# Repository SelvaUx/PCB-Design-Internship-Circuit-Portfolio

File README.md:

<h1 align="center">⚡ PCB Design Internship — Circuit Portfolio</h1>

<p align="center">
  <strong>A collection of 10 production-ready schematic & PCB layout designs</strong><br/>
  <em>From fundamental analog circuits to motor control systems — all designed in KiCad</em>
</p>

---

## 👤 About the Author

**Selva Pandi** — _Selva.Ux_ online

> An ECE student who decided that waiting to be qualified was a worse plan than just building the thing.

I build for the messy, low-bandwidth, real world — where people need technology that actually functions. My engineering philosophy is simple: **offline first, privacy always, real hardware required**. I don't trust solutions that work only in ideal conditions.

From custom AI assistants to fiber fault detection engines, from IoT aquaculture platforms to portfolio sites with mini-labs inside — the list doesn't stop because the curiosity doesn't stop.

|                        |                                                            |
| ---------------------- | ---------------------------------------------------------- |
| 🌐 **Portfolio + Lab** | [selvaux.in](https://selvaux.in)                           |
| 📫 **Email**           | [selva.ux@yahoo.com](mailto:selva.ux@yahoo.com)            |
| 💡 **Specialization**  | Offline AI · Edge Computing · Embedded Systems · Custom OS |

---

## 🛠️ Tools & Technologies

| Tool                                            | Purpose                                                             |
| ----------------------------------------------- | ------------------------------------------------------------------- |
| [**KiCad EDA**](https://www.kicad.org/) (v10.0) | Primary CAD suite                                                   |
| **Eeschema**                                    | Schematic capture, including hierarchical multi-sheet designs       |
| **Pcbnew**                                      | PCB routing, footprint assignment, copper zone fills & board layout |
| **SPICE**                                       | Integrated simulation models for circuit verification               |

---

## 📂 Repository Structure

```
📦 Iternship PCB/
├── 🌉 Bridge Rectifier/          → Full-wave AC-to-DC rectifier
├── 🚨 Buzzer Alarm/              → Transistor-driven buzzer with push-button
├── 💡 LED Blink Using IC555/     → Astable multivibrator LED flasher
├── 🔌 LED Circuit/               → Multi-LED driver with transistor switching
├── 📉 Low Pass Filter/           → Passive RC low-pass filter
├── 🎵 METRONOME/                 → 555 Timer metronome with speaker output
├── ⚙️ Motor Speed Controller/    → PWM DC motor speed control via L293 H-Bridge
├── 💡 Simple LED Circuit/        → Hierarchical push-button LED (multi-sheet)
├── ⚡ Voltage Divider/           → Two-resistor voltage divider
├── 🔌 Voltage Regulator/         → +5V linear regulated power supply
└── 📄 README.md
```

Each project folder contains:

```text
├── [Project].kicad_pro     # KiCad Project File
├── [Project].kicad_sch     # Main Schematic (or Parent Sheet)
├── [Project].kicad_pcb     # PCB Layout File
├── [Project].kicad_prl     # Project Local Settings
├── [Sub-sheets].kicad_sch  # Sub-schematics (hierarchical designs only)
└── .history/               # KiCad automatic local history backups
```

---

## 📋 Projects Catalog

### 1. 🌉 Bridge Rectifier

|               |                                               |
| ------------- | --------------------------------------------- |
| **Category**  | Power Electronics — AC/DC Conversion          |
| **Schematic** | `Bridge Rectifier/Bridge Rectifier.kicad_sch` |
| **PCB**       | `Bridge Rectifier/Bridge Rectifier.kicad_pcb` |

**Circuit Goal:** Converts a dual AC voltage source into a smoothed, single-polarity DC output.

**Bill of Materials:**

| Ref    | Component                        | Value    | Purpose                    |
| ------ | -------------------------------- | -------- | -------------------------- |
| D1–D4  | `1N4007` Rectifier Diode         | —        | Bridge configuration       |
| C1     | Polarized Electrolytic Capacitor | `4000µF` | Ripple smoothing reservoir |
| R1     | Resistor                         | `1kΩ`    | Load / bleeder resistor    |
| V1, V2 | Sinusoidal AC Source             | `12V`    | Simulation sources         |

**How It Works:** The four diodes form a bridge that rectifies both halves of the AC waveform. The large `4000µF` capacitor acts as a low-pass reservoir to minimize voltage ripple, delivering a stable DC output across `R1`.

---

### 2. 🚨 Buzzer Alarm

|               |                                       |
| ------------- | ------------------------------------- |
| **Category**  | Digital Logic — Transistor Switching  |
| **Schematic** | `Buzzer Alarm/Buzzer Alarm.kicad_sch` |
| **PCB**       | `Buzzer Alarm/Buzzer Alarm.kicad_pcb` |

**Circuit Goal:** A transistor-driven active buzzer alarm actuated by a manual push-button switch.

**Bill of Materials:**

| Ref | Component          | Value  | Purpose                    |
| --- | ------------------ | ------ | -------------------------- |
| BZ1 | Active Buzzer      | —      | Sound output               |
| Q1  | `BC547` NPN BJT    | —      | Low-side electronic switch |
| SW1 | Push Button (SPST) | —      | Manual trigger             |
| R1  | Resistor           | `10kΩ` | Base current-limiting      |
| R2  | Resistor           | `1kΩ`  | Bias resistor              |

**How It Works:** The `BC547` transistor acts as a low-side switch. Pressing `SW1` drives base current into `Q1` via `R1`, saturating the transistor and allowing current to flow through the buzzer to ground.

---

### 3. ⏱️ LED Blink Using IC555

|               |                                                         |
| ------------- | ------------------------------------------------------- |
| **Category**  | Timing & Oscillation — Astable Multivibrator            |
| **Schematic** | `LED Blink Using IC555/LED Blink Using IC555.kicad_sch` |
| **PCB**       | `LED Blink Using IC555/LED Blink Using IC555.kicad_pcb` |

**Circuit Goal:** A classic 555 Timer astable oscillator that pulses an LED indicator at a defined frequency.

**Bill of Materials:**

| Ref | Component            | Value    | Purpose                           |
| --- | -------------------- | -------- | --------------------------------- |
| U1  | `NA555P` Timer IC    | —        | Oscillator core                   |
| R1  | Timing Resistor      | `1MΩ`    | Controls charge time T_high       |
| R2  | Timing Resistor      | `1MΩ`    | Controls charge & discharge T_low |
| C1  | Timing Capacitor     | `1.5nF`  | RC timing element                 |
| C2  | Bypass Capacitor     | `0.01µF` | Control voltage pin decoupling    |
| D1  | Red LED              | —        | Pulse indicator                   |
| R3  | Resistor             | `470Ω`   | LED current-limiting              |
| J1  | 2-pin Screw Terminal | —        | Power input connector             |

**How It Works:** The 555 continuously charges and discharges `C1` between ⅓ and ⅔ of VCC through `R1` and `R2`. This produces a continuous square wave on pin 3 (Output), causing LED `D1` to flash at a rate defined by:

$$f = \frac{1.44}{(R1 + 2 \cdot R2) \cdot C1}$$

---

### 4. 🔌 LED Circuit

|               |                                         |
| ------------- | --------------------------------------- |
| **Category**  | Transistor Switching — Multi-LED Driver |
| **Schematic** | `LED Circuit/LED Circuit.kicad_sch`     |
| **PCB**       | `LED Circuit/LED Circuit.kicad_pcb`     |

**Circuit Goal:** A multi-channel LED driver circuit using `BC547` NPN transistors as electronic switches, each controlling individual LEDs through current-limiting resistors.

**Bill of Materials:**

| Ref   | Component       | Value  | Purpose               |
| ----- | --------------- | ------ | --------------------- |
| BT1   | Battery Cell    | —      | DC power source       |
| Q1–Q3 | `BC547` NPN BJT | —      | LED driver switches   |
| D1–D9 | LEDs            | —      | Light indicators      |
| R1–R3 | Resistor        | `470Ω` | LED current-limiting  |
| R4–R6 | Resistor        | `10kΩ` | Base current-limiting |
| C1–C3 | Capacitor       | —      | Decoupling / timing   |

**How It Works:** Each `BC547` transistor is independently driven via a base resistor. When the transistor is saturated, it provides a ground path for the corresponding LED string. The `470Ω` resistors limit LED forward current, and `10kΩ` resistors control transistor base drive. This design demonstrates parallel transistor switching for multi-LED arrays.

---

### 5. 📉 Low Pass Filter

|               |                                             |
| ------------- | ------------------------------------------- |
| **Category**  | Signal Conditioning — Passive Filter        |
| **Schematic** | `Low Pass Filter/Low Pass Filter.kicad_sch` |
| **PCB**       | `Low Pass Filter/Low Pass Filter.kicad_pcb` |

**Circuit Goal:** A basic passive single-pole RC Low Pass Filter (LPF).

**Bill of Materials:**

| Ref | Component            | Value | Purpose        |
| --- | -------------------- | ----- | -------------- |
| R1  | Resistor             | `1kΩ` | Filter element |
| C1  | Polarized Capacitor  | `1µF` | Filter element |
| J1  | 2-pin Screw Terminal | —     | I/O connector  |

**How It Works:** Attenuates high-frequency signals while passing lower-frequency components. The cutoff frequency is:

$$f_c = \frac{1}{2\pi \cdot R1 \cdot C1} \approx 159.15 \text{ Hz}$$

Signals above this frequency are progressively attenuated at –20 dB/decade.

---

### 6. 🎵 METRONOME

|               |                                          |
| ------------- | ---------------------------------------- |
| **Category**  | Timing & Audio — Audible Click Generator |
| **Schematic** | `METRONOME/METRONOME.kicad_sch`          |
| **PCB**       | `METRONOME/METRONOME.kicad_pcb`          |

**Circuit Goal:** A 555 Timer-based electronic metronome that generates periodic audible clicks through a speaker, with adjustable tempo via a variable resistor (potentiometer).

**Bill of Materials:**

| Ref   | Component         | Value | Purpose                       |
| ----- | ----------------- | ----- | ----------------------------- |
| IC555 | 555 Timer IC      | —     | Astable oscillator core       |
| BT1   | Battery Cell      | —     | DC power source               |
| LS1   | Speaker           | —     | Audio output (CUI CMR-1206S)  |
| R1    | Resistor          | —     | Timing resistor               |
| R2    | Variable Resistor | —     | Tempo control (potentiometer) |
| R3    | Variable Resistor | —     | Fine tuning                   |
| C1–C3 | Capacitors        | —     | Timing & decoupling           |

**How It Works:** The 555 Timer runs in astable mode, generating a square wave output. The variable resistors `R2` and `R3` allow the user to adjust the oscillation frequency (tempo). The output drives a speaker `LS1` to produce rhythmic audible clicks. The timing capacitor and RC network set the beat interval.

---

### 7. ⚙️ Motor Speed Controller

|               |                                                           |
| ------------- | --------------------------------------------------------- |
| **Category**  | Motor Control — PWM Speed Regulation                      |
| **Schematic** | `Motor Speed Controller/Motor Speed Controller.kicad_sch` |
| **PCB**       | `Motor Speed Controller/Motor Speed Controller.kicad_pcb` |

**Circuit Goal:** A PWM-based DC motor speed controller using a 555 Timer IC for pulse generation and an L293 Quadruple Half-H Driver for motor drive, with flyback protection and direction control.

**Bill of Materials:**

| Ref    | Component              | Value  | Purpose                           |
| ------ | ---------------------- | ------ | --------------------------------- |
| U1     | `ICM7555xP` Timer IC   | —      | PWM pulse generator (astable)     |
| U2     | `L293` Motor Driver    | —      | Quadruple Half-H bridge driver    |
| M1     | DC Motor               | —      | Load                              |
| D2, D3 | `1N4001` Diode         | —      | Flyback / freewheeling protection |
| SW1    | Nidec CAS-120A1 Switch | —      | Motor on/off control              |
| R1     | Resistor               | `1kΩ`  | Timing / bias                     |
| R2, R4 | Resistor               | `100Ω` | Current limiting                  |
| R3     | Resistor               | —      | Timing                            |
| C1     | Polarized Capacitor    | `10µF` | Timing / decoupling               |
| J1     | 2-pin Screw Terminal   | —      | Power input connector             |

**How It Works:** The `ICM7555` generates a variable-duty-cycle PWM signal that feeds into the L293 H-Bridge driver's enable and input pins. By varying the duty cycle, the average voltage delivered to the DC motor changes, controlling its speed. The `1N4001` diodes provide flyback protection against voltage spikes from the motor's inductive load. The L293 handles the power switching, isolating the low-power timer circuit from the high-current motor.

---

### 8. 💡 Simple LED Circuit

|               |                                                            |
| ------------- | ---------------------------------------------------------- |
| **Category**  | Digital Basics — Hierarchical Design                       |
| **Schematic** | `Simple LED Circuit/Simple LED Circuit.kicad_sch` (Master) |
| **PCB**       | `Simple LED Circuit/Simple LED Circuit.kicad_pcb`          |

**Circuit Goal:** A modular, push-button-activated LED circuit using a **multi-sheet hierarchical design** in KiCad.

**Schematic Architecture:**

| Sheet                                       | Components                                 | Role                        |
| ------------------------------------------- | ------------------------------------------ | --------------------------- |
| **Master** (`Simple LED Circuit.kicad_sch`) | —                                          | Declares & links sub-sheets |
| **Power** (`power.kicad_sch`)               | `BT2`: Battery, `SW2`: Push Button         | Power supply & control      |
| **LED** (`led.kicad_sch`)                   | `D2`: LED, `R2`: Current-Limiting Resistor | Load & indicator            |

**How It Works:** When the button is held down, current flows from the battery through the resistor and lights the LED. This project demonstrates clean, modular circuit design using KiCad's hierarchical page linking system.

---

### 9. ⚡ Voltage Divider

|               |                                               |
| ------------- | --------------------------------------------- |
| **Category**  | Analog Fundamentals — Passive Voltage Scaling |
| **Schematic** | `Voltage Divider/Voltage Divider.kicad_sch`   |
| **PCB**       | `Voltage Divider/Voltage Divider.kicad_pcb`   |

**Circuit Goal:** A fundamental two-resistor voltage divider to step down DC voltage.

**Bill of Materials:**

| Ref | Component         | Value | Purpose            |
| --- | ----------------- | ----- | ------------------ |
| V1  | DC Voltage Source | `5V`  | Input (simulation) |
| R1  | Resistor          | `1kΩ` | Upper divider arm  |
| R2  | Resistor          | `1kΩ` | Lower divider arm  |

**How It Works:** Splits the input voltage proportionally to the resistor ratio. With two equal `1kΩ` resistors:

$$V_{out} = V_{in} \cdot \frac{R2}{R1 + R2} = 5\text{V} \cdot \frac{1\text{k}\Omega}{2\text{k}\Omega} = 2.5\text{V}$$

---

### 10. 🔌 Voltage Regulator (+5V Linear Power Supply)

|               |                                                 |
| ------------- | ----------------------------------------------- |
| **Category**  | Power Electronics — Linear Regulated Supply     |
| **Schematic** | `Voltage Regulator/Voltage Regulator.kicad_sch` |
| **PCB**       | `Voltage Regulator/Voltage Regulator.kicad_pcb` |

**Circuit Goal:** A complete +5V regulated linear power supply that rectifies AC input, filters noise, and outputs a stable 5V DC rail.

**Bill of Materials:**

| Ref   | Component                        | Value    | Purpose                      |
| ----- | -------------------------------- | -------- | ---------------------------- |
| D1–D4 | `1N4007` Rectifier Diode         | —        | Full-wave bridge rectifier   |
| U1    | `L7805` Linear Voltage Regulator | +5V      | Voltage regulation           |
| C1    | Electrolytic Capacitor           | `2200µF` | Reservoir / ripple smoothing |
| C2    | Capacitor                        | `10µF`   | Output decoupling            |
| D5    | Green LED                        | —        | Power-on indicator           |
| R1    | Resistor                         | `330Ω`   | LED current-limiting         |
| J1    | 2-pin Screw Terminal             | —        | AC/DC input connector        |
| J2    | 2-pin Screw Terminal             | —        | +5V / GND output connector   |

**How It Works:** AC input is rectified by the diode bridge, filtered by the `2200µF` reservoir capacitor, and then regulated to a stable +5V by the L7805 linear regulator. The `10µF` output capacitor filters high-frequency transients. A green LED with a `330Ω` resistor provides a visual power-on indicator.

---

## 📊 Project Complexity Matrix

| #   | Project                | Components | IC Used        | Design       | Has PCB |
| --- | ---------------------- | ---------- | -------------- | ------------ | ------- |
| 1   | Bridge Rectifier       | 7          | —              | Flat         | ✅      |
| 2   | Buzzer Alarm           | 5          | —              | Flat         | ✅      |
| 3   | LED Blink (IC555)      | 8          | NE555          | Flat         | ✅      |
| 4   | LED Circuit            | 20+        | —              | Flat         | ✅      |
| 5   | Low Pass Filter        | 3          | —              | Flat         | ✅      |
| 6   | Metronome              | 8+         | 555 Timer      | Flat         | ✅      |
| 7   | Motor Speed Controller | 12+        | ICM7555 + L293 | Flat         | ✅      |
| 8   | Simple LED Circuit     | 4          | —              | Hierarchical | ✅      |
| 9   | Voltage Divider        | 3          | —              | Flat         | ✅      |
| 10  | Voltage Regulator      | 9          | L7805          | Flat         | ✅      |

---

## 🧠 Key Concepts Demonstrated

| Concept                           | Projects                                     |
| --------------------------------- | -------------------------------------------- |
| **AC/DC Rectification**           | Bridge Rectifier, Voltage Regulator          |
| **555 Timer (Astable Mode)**      | LED Blink, Metronome, Motor Speed Controller |
| **Transistor Switching (BJT)**    | Buzzer Alarm, LED Circuit                    |
| **Passive Filters (RC)**          | Low Pass Filter                              |
| **Voltage Regulation**            | Voltage Regulator (L7805)                    |
| **Motor Drive (H-Bridge)**        | Motor Speed Controller (L293)                |
| **Hierarchical Schematic Design** | Simple LED Circuit                           |
| **PWM Speed Control**             | Motor Speed Controller                       |

---

## 🚀 Getting Started

### Prerequisites

- **[KiCad 8.0+](https://www.kicad.org/download/)** installed on your system (v10.0 recommended)

### Opening a Project

1. Clone or download this repository:
   ```bash
   git clone https://github.com/selvaux/PCB-Design-Internship-Circuit-Portfolio.git
   ```
2. Open **KiCad** and go to **File → Open Project...**
3. Navigate to any subfolder (e.g., `Motor Speed Controller/`)
4. Select the `.kicad_pro` file to launch the project
5. From the project manager:
   - Double-click `.kicad_sch` → View & edit schematics
   - Double-click `.kicad_pcb` → View PCB layout & routing

### Simulation

Many projects include SPICE simulation models. To simulate:

1. Open the schematic in Eeschema
2. Go to **Inspect → Simulator**
3. Configure and run your simulation

---

## 📜 License

This project is open source and available for educational purposes.

---

<p align="center">
  <strong>Built with ⚡ by <a href="https://selvaux.in">Selva Pandi</a></strong><br/>
  <em>Offline AI · Edge Computing · Embedded Systems · Custom OS</em><br/><br/>
  <sub>✨ The curiosity doesn't stop — neither does the work.</sub>
</p>

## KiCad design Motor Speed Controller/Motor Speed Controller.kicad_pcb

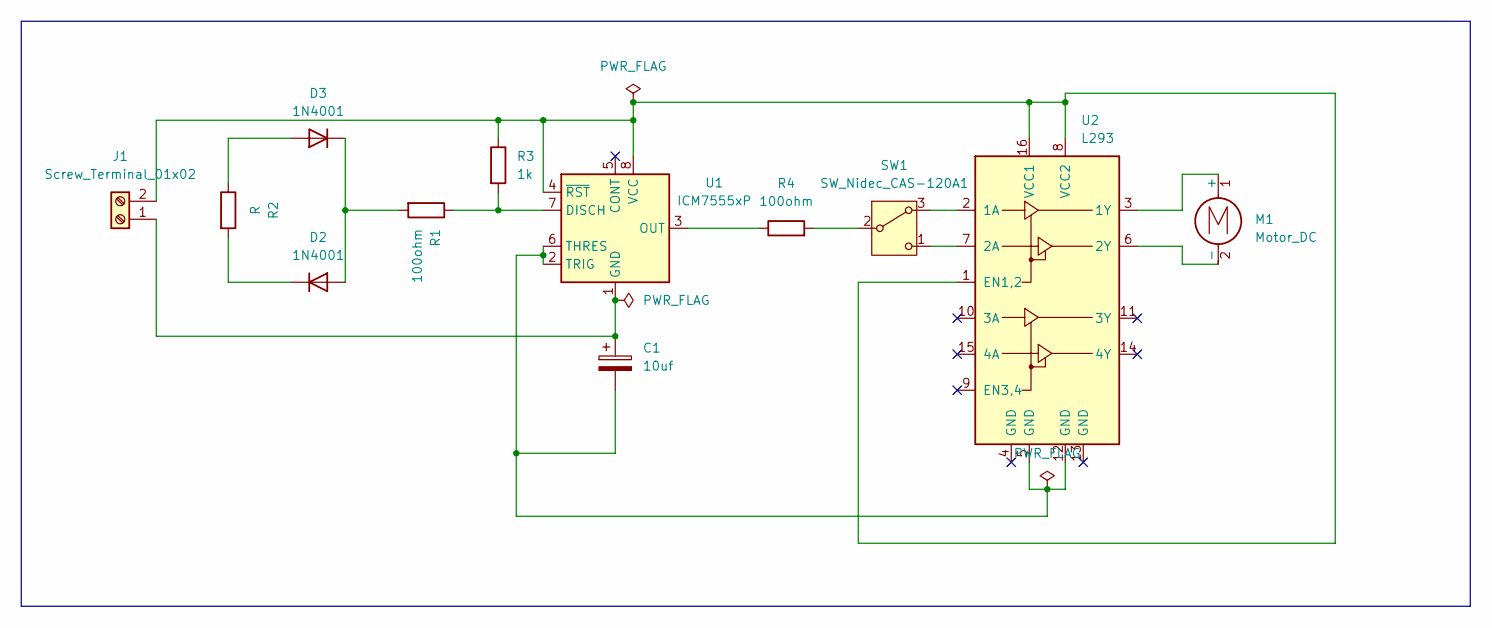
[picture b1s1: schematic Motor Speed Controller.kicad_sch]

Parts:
C1: 10uf; CP_Radial_D10.0mm_P5.00mm
D2, D3: 1N4001; D_DO-41_SOD81_P10.16mm_Horizontal
J1: Screw_Terminal_01x02; TerminalBlock_Phoenix_MKDS-1,5-2-5.08_1x02_P5.08mm_Horizont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
M1: Motor_DC; TerminalBlock_Phoenix_MKDS-1,5-2-5.08_1x02_P5.08mm_Horizont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
R1, R4: 100ohm; R_Axial_DIN0207_L6.3mm_D2.5mm_P10.16mm_Horizontal
R2: R; R_Axial_DIN0207_L6.3mm_D2.5mm_P10.16mm_Horizontal
R3: 1k; R_Axial_DIN0207_L6.3mm_D2.5mm_P10.16mm_Horizontal
SW1: SW_Nidec_CAS-120A1; PinHeader_1x03_P1.00mm_Vertical
U1: ICM7555xP; DIP-8_W7.62mm
U2: L293; DIP-16_W7.62mm

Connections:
unnamed: D2.2 (A), D3.1 (K), R1.2
unnamed: D2.1 (K), R2.2
unnamed: D3.2 (A), R2.1
unnamed: C1.1, J1.1, U1.1 (GND)
unnamed: J1.2, R3.1, U1.4 (~RST), U1.8 (VCC), U2.1 (EN1,2), U2.8 (VCC2), U2.16 (VCC1)
unnamed: M1.1 (+), U2.3 (1Y)
unnamed: M1.2 (-), U2.6 (2Y)
unnamed: SW1.3 (A), U2.2 (1A)
unnamed: R4.2, SW1.2 (B)
unnamed: SW1.1 (C), U2.7 (2A)
unnamed: R1.1, R3.2, U1.7 (DISCH)
unnamed: R4.1, U1.3 (OUT)
unnamed: C1.2, U1.2 (TRIG), U1.6 (THRES), U2.5 (GND), U2.12 (GND)

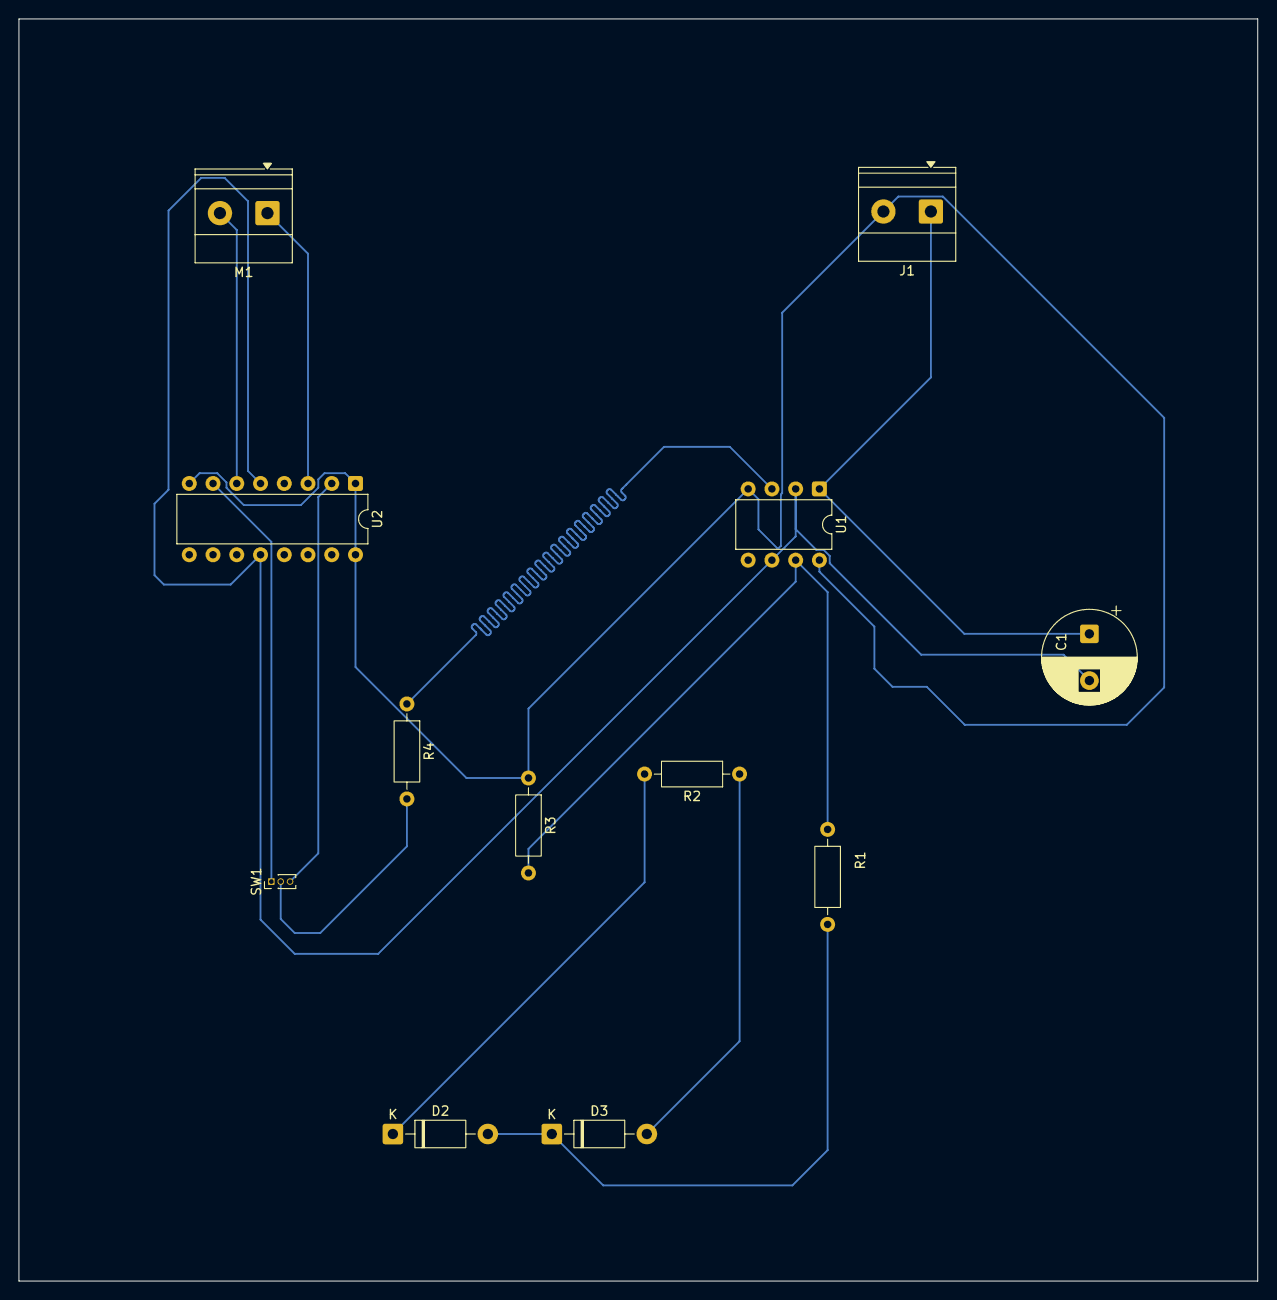
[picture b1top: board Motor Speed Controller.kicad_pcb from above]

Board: 2 copper layers, 132.5 x 135.0 mm, 12 parts (0 on the bottom side), 13 nets.

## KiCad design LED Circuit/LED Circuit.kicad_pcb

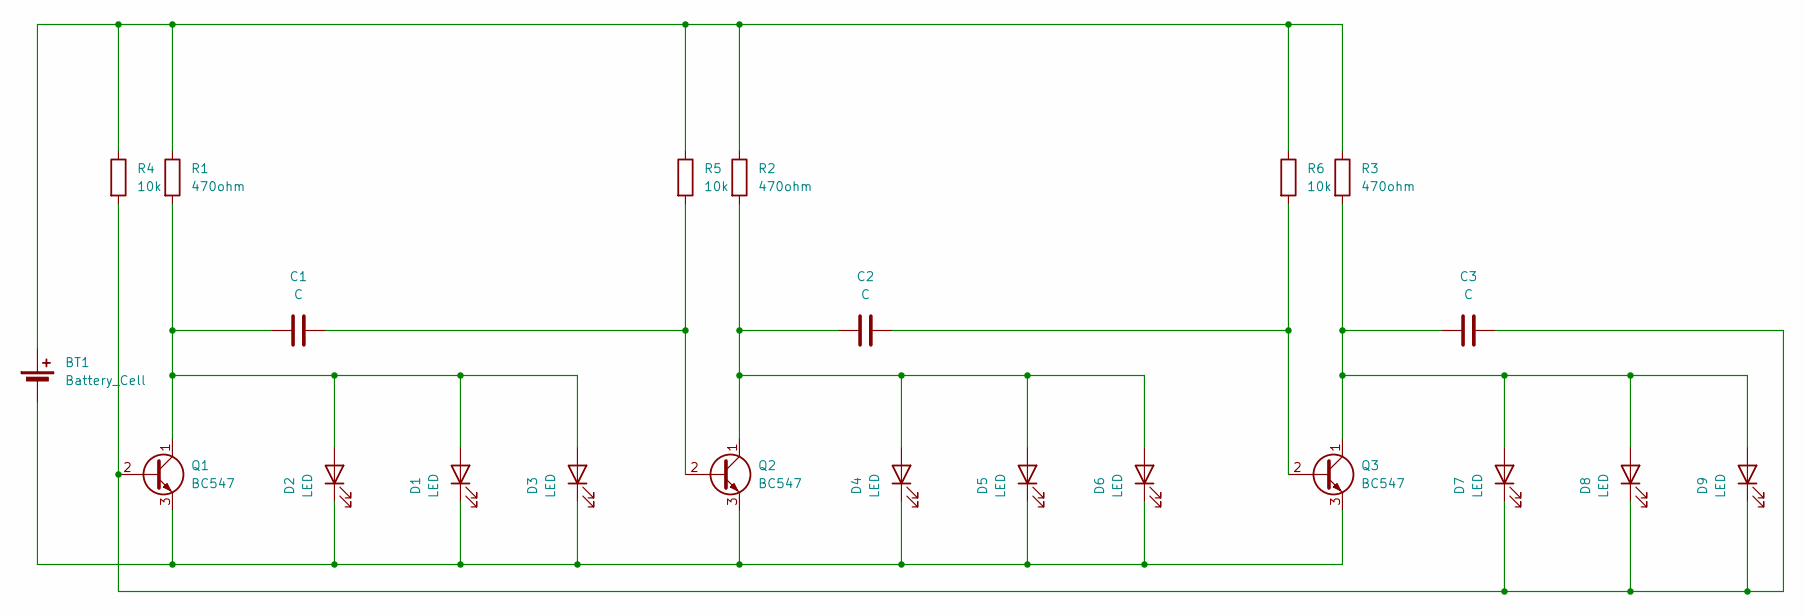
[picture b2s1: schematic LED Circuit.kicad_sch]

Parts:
BT1: Battery_Cell; BatteryHolder_Keystone_2466_1xAAA
C1, C2, C3: C; CP_Radial_D10.0mm_P5.00mm
D1, D2, D3, D4, D5, D6, D7, D8, D9: LED; LED_0402_1005Metric
Q1, Q2, Q3: BC547; TO-92_Inline
R1, R2, R3: 470ohm; R_Axial_DIN0207_L6.3mm_D2.5mm_P10.16mm_Horizontal
R4, R5, R6: 10k; R_Axial_DIN0207_L6.3mm_D2.5mm_P10.16mm_Horizontal

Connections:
unnamed: BT1.1 (+), R1.1, R2.1, R3.1, R4.1, R5.1, R6.1
unnamed: BT1.2 (-), D1.1 (K), D2.1 (K), D3.1 (K), D4.1 (K), D5.1 (K), D6.1 (K), Q1.3 (E), Q2.3 (E), Q3.3 (E)
unnamed: C1.1, D1.2 (A), D2.2 (A), D3.2 (A), Q1.1 (C), R1.2
unnamed: C2.1, D4.2 (A), D5.2 (A), D6.2 (A), Q2.1 (C), R2.2
unnamed: C3.1, D7.2 (A), D8.2 (A), D9.2 (A), Q3.1 (C), R3.2
unnamed: C3.2, D7.1 (K), D8.1 (K), D9.1 (K), Q1.2 (B), R4.2
unnamed: C1.2, Q2.2 (B), R5.2
unnamed: C2.2, Q3.2 (B), R6.2

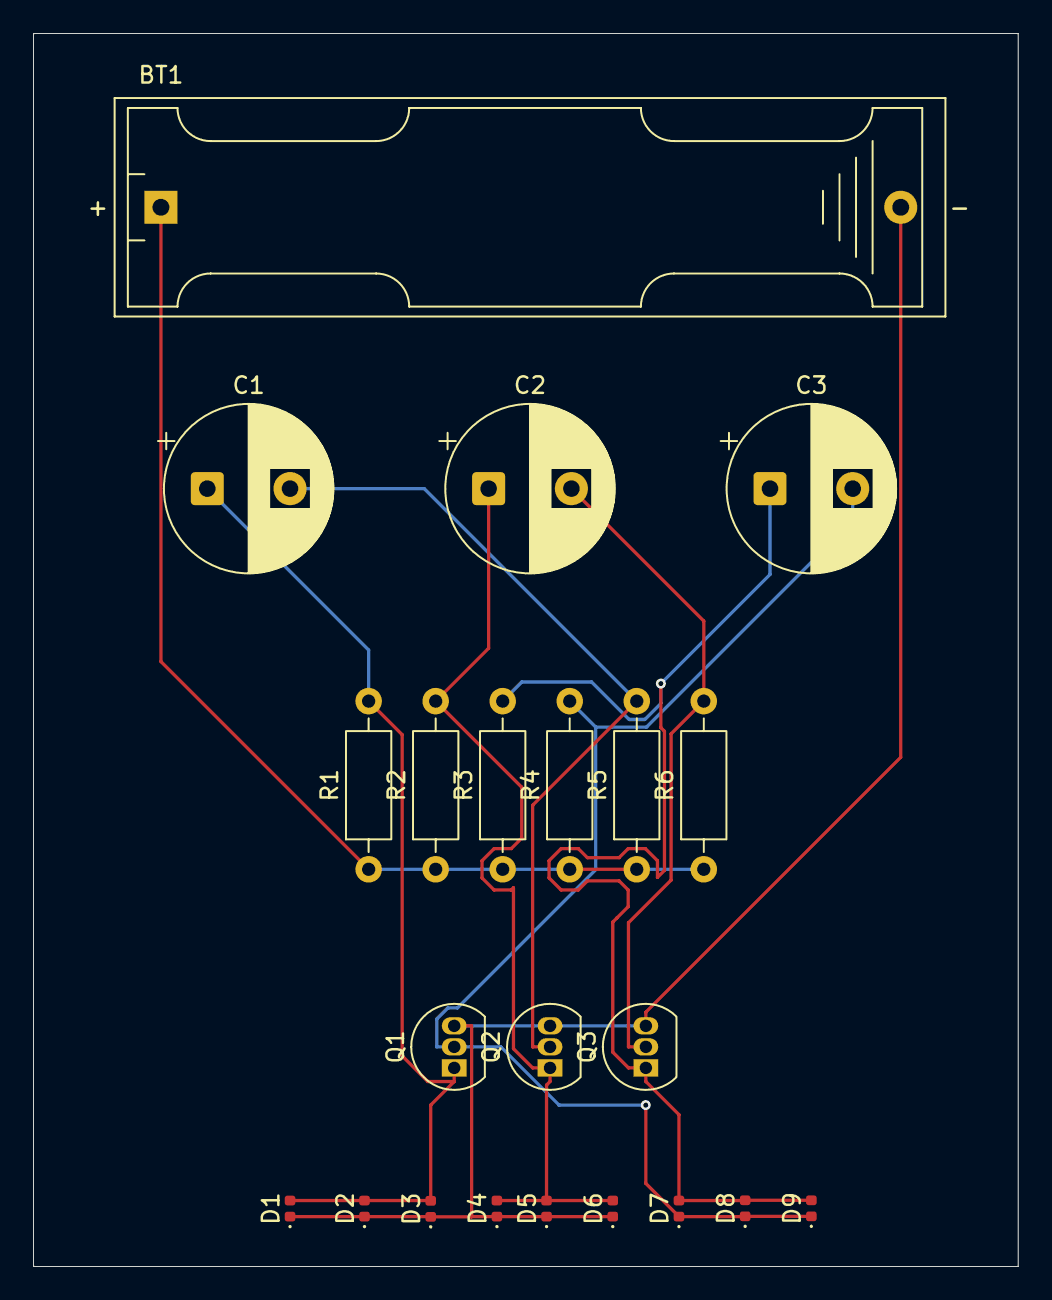
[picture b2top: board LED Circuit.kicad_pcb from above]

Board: 2 copper layers, 59.5 x 74.5 mm, 22 parts (0 on the bottom side), 8 nets.

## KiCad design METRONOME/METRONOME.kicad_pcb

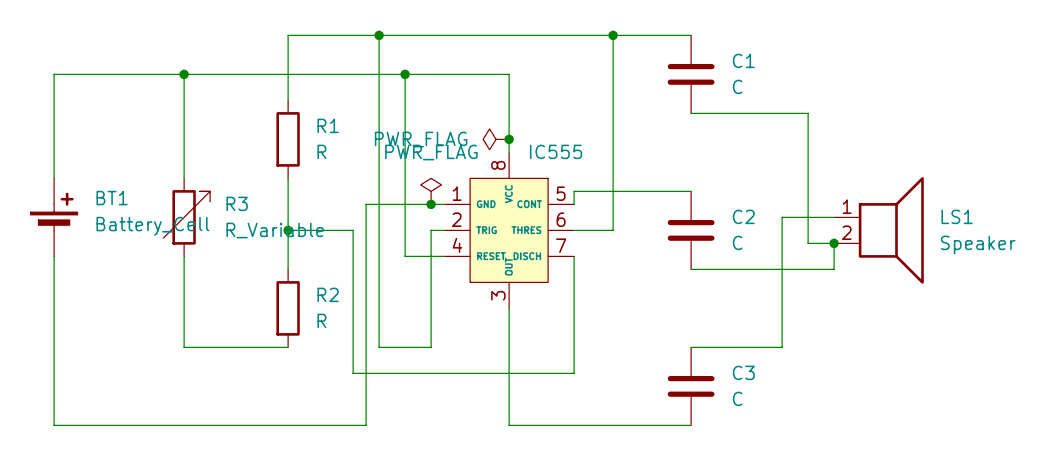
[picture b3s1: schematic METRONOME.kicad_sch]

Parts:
BT1: Battery_Cell; BatteryHolder_Keystone_2466_1xAAA
C1, C2, C3: C; CP_Radial_D10.0mm_P5.00mm
IC555: SOIC-8_3.9x4.9mm_P1.27mm
LS1: Speaker; Speaker_CUI_CMR-1206S-67
R1, R2: R; R_Axial_DIN0207_L6.3mm_D2.5mm_P10.16mm_Horizontal
R3: R_Variable; Potentiometer_Bourns_3266Y_Vertical

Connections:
unnamed: BT1.1 (+), IC555.4 (RESET), IC555.8 (VCC), R3.1
unnamed: BT1.2 (-), IC555.1 (GND)
unnamed: C1.2, C2.2, LS1.2
unnamed: C3.1, LS1.1
unnamed: C2.1, IC555.5 (CONT)
unnamed: IC555.7 (DISCH), R1.2, R2.1
unnamed: C3.2, IC555.3 (OUT)
unnamed: C1.1, IC555.2 (TRIG), IC555.6 (THRES), R1.1
unnamed: R2.2, R3.2

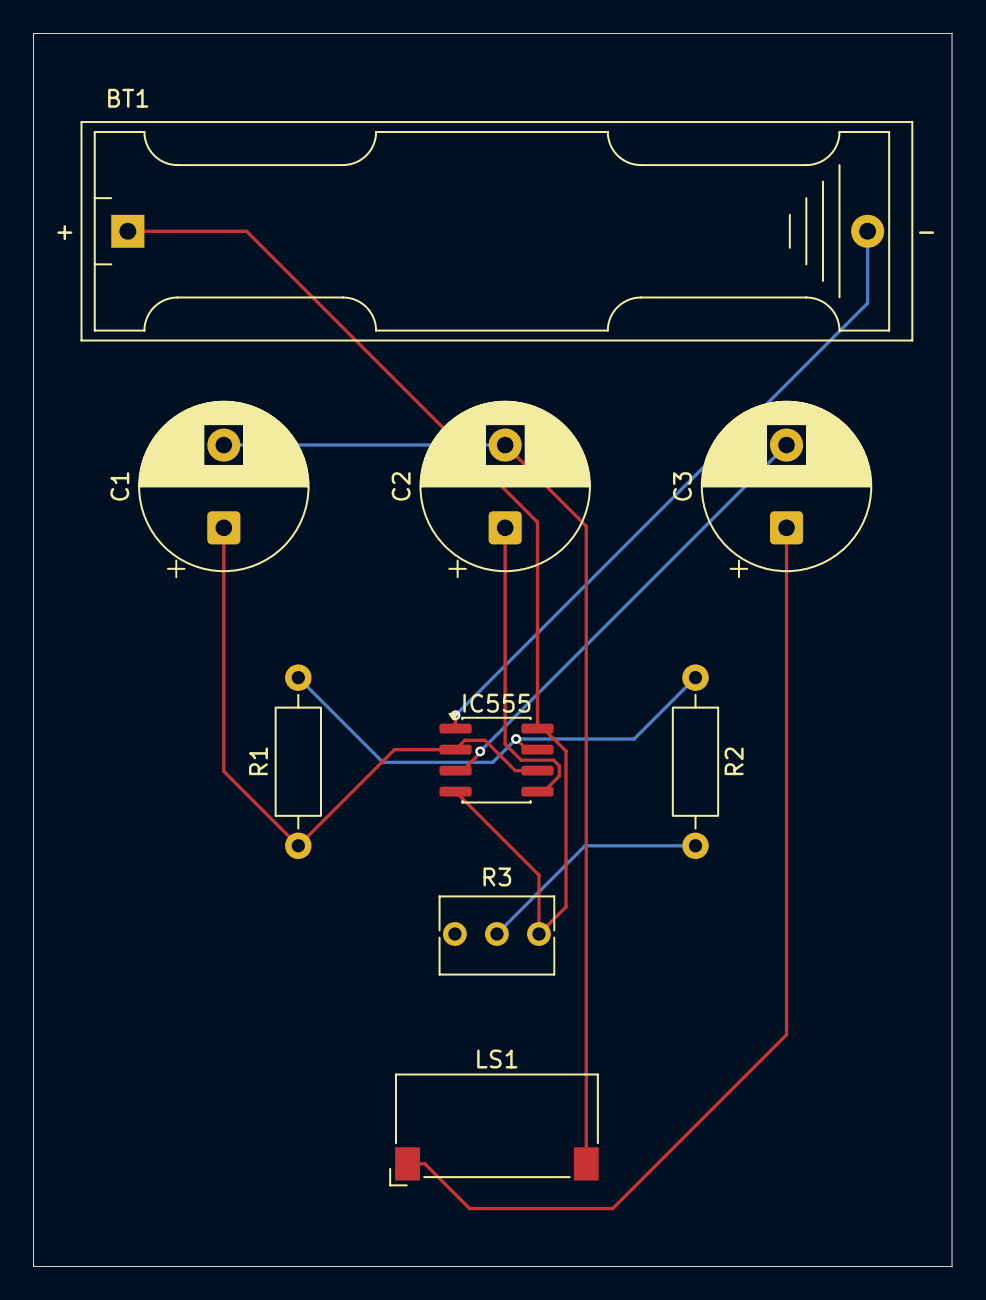
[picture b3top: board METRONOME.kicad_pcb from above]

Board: 2 copper layers, 55.5 x 74.5 mm, 9 parts (0 on the bottom side), 9 nets.

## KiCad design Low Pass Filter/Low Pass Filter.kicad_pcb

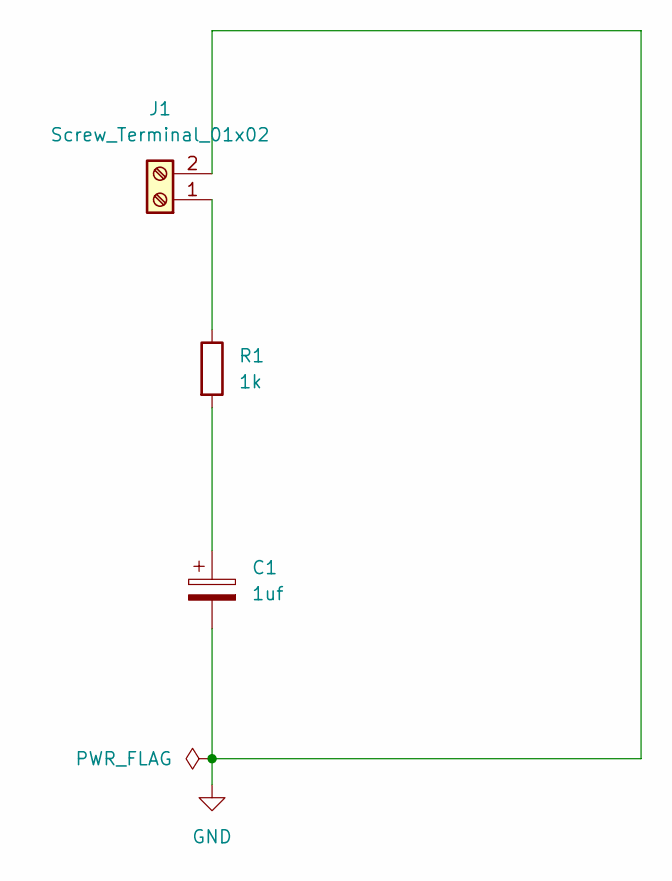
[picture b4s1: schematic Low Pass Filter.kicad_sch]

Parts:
C1: 1uf; CP_Radial_D12.5mm_P5.00mm
J1: Screw_Terminal_01x02; PinHeader_1x02_P2.54mm_Vertical
R1: 1k; R_Axial_DIN0207_L6.3mm_D2.5mm_P7.62mm_Horizontal

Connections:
GND: C1.2, J1.2
unnamed: C1.1, R1.2
unnamed: J1.1, R1.1

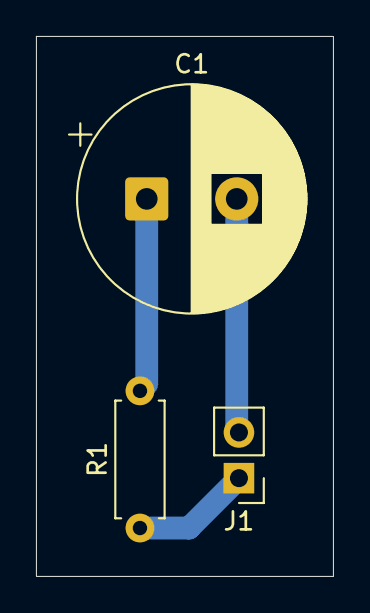
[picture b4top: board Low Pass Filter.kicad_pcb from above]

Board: 2 copper layers, 16.5 x 30.0 mm, 3 parts (0 on the bottom side), 3 nets.

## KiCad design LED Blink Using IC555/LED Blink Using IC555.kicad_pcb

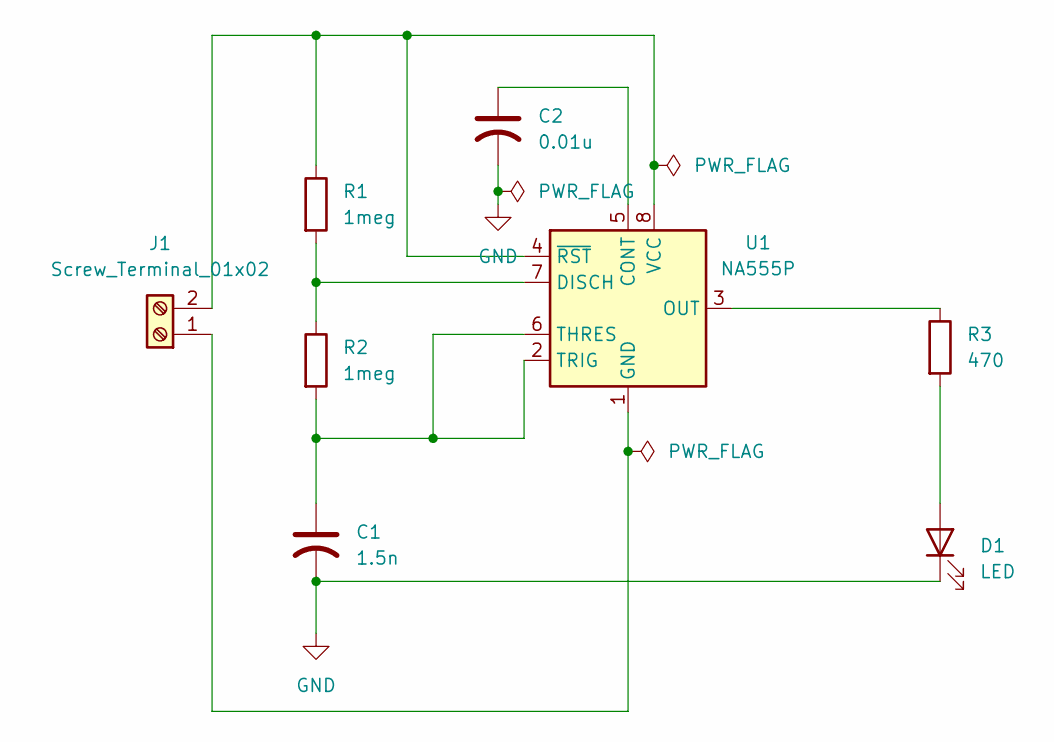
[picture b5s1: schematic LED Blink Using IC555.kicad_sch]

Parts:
C1: 1.5n; CP_Radial_D12.5mm_P5.00mm
C2: 0.01u; CP_Radial_D12.5mm_P5.00mm
D1: LED; LED_D5.0mm
J1: Screw_Terminal_01x02; TerminalBlock_Phoenix_MKDS-1,5-2_1x02_P5.00mm_Horizontal
R1, R2: 1meg; R_Axial_DIN0207_L6.3mm_D2.5mm_P7.62mm_Horizontal
R3: 470; R_Axial_DIN0207_L6.3mm_D2.5mm_P7.62mm_Horizontal
U1: NA555P; DIP-8_W7.62mm

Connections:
GND: C1.2, C2.2, D1.1 (K)
unnamed: D1.2 (A), R3.2
unnamed: J1.1, U1.1 (GND)
unnamed: J1.2, R1.1, U1.4 (~RST), U1.8 (VCC)
unnamed: C2.1, U1.5 (CONT)
unnamed: R1.2, R2.1, U1.7 (DISCH)
unnamed: R3.1, U1.3 (OUT)
unnamed: C1.1, R2.2, U1.2 (TRIG), U1.6 (THRES)

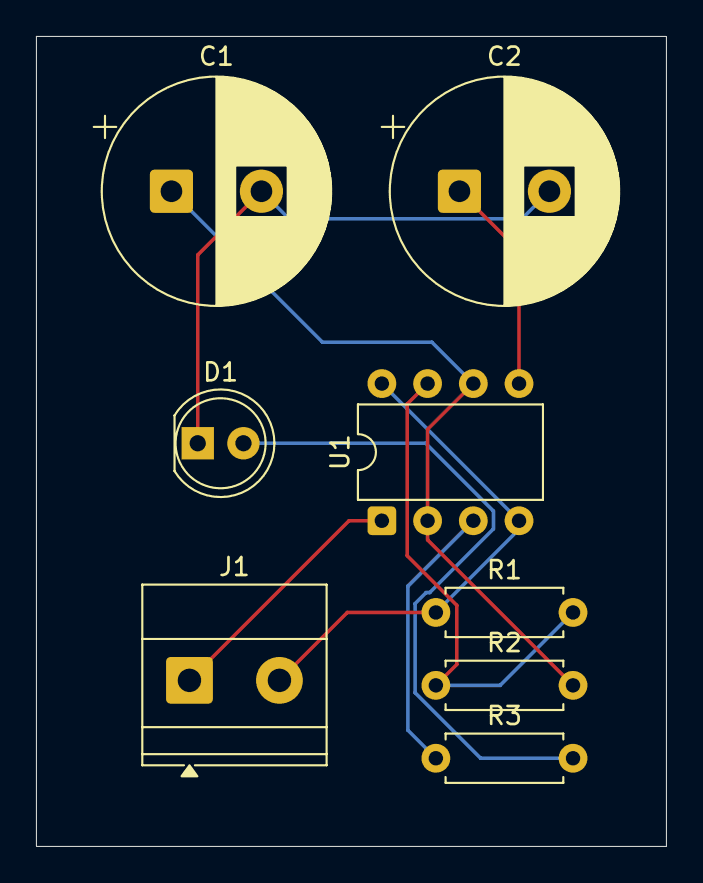
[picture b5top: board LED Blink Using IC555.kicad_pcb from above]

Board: 2 copper layers, 35.0 x 45.0 mm, 8 parts (0 on the bottom side), 8 nets.

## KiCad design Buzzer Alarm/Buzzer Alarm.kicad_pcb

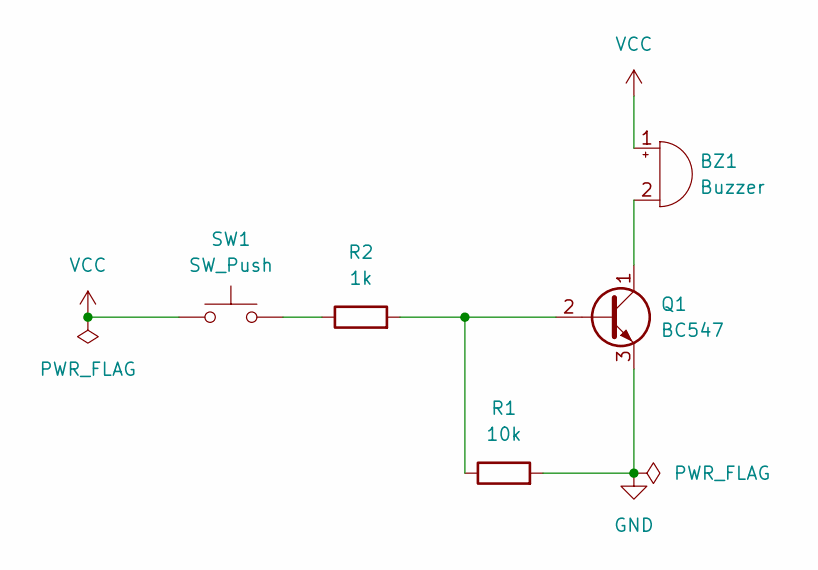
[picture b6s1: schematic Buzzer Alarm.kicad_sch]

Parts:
BZ1: Buzzer; Buzzer_TDK_PS1240P02BT_D12.2mm_H6.5mm
Q1: BC547; TO-92_Inline
R1: 10k; R_Axial_DIN0207_L6.3mm_D2.5mm_P7.62mm_Horizontal
R2: 1k; R_Axial_DIN0207_L6.3mm_D2.5mm_P7.62mm_Horizontal
SW1: SW_Push; SW_PUSH_1P1T_6x3.5mm_H4.3_APEM_MJTP1243

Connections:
GND: Q1.3 (E), R1.2
unnamed: BZ1.2 (-), Q1.1 (C)
unnamed: Q1.2 (B), R1.1, R2.2
unnamed: R2.1, SW1.2
VCC: BZ1.1 (+), SW1.1

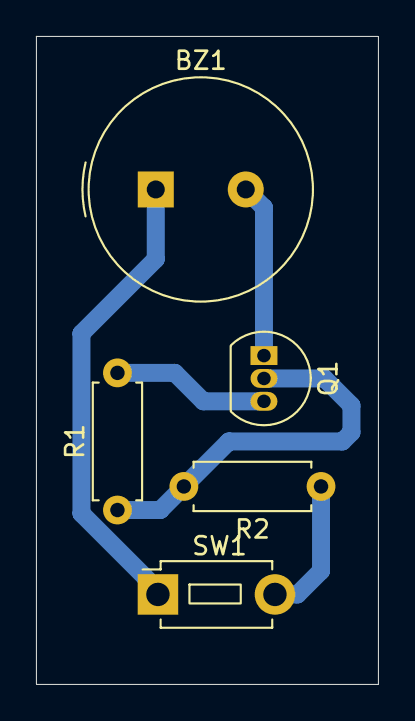
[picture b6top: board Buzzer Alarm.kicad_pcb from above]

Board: 2 copper layers, 19.0 x 36.0 mm, 5 parts (0 on the bottom side), 5 nets.

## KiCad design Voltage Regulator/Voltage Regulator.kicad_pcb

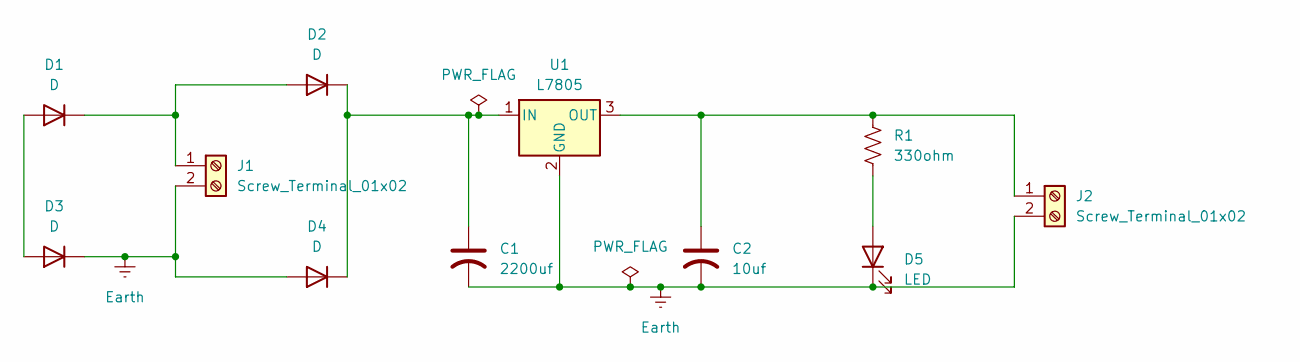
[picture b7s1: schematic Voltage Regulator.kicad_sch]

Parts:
C1: 2200uf; CP_Radial_D12.5mm_P5.00mm
C2: 10uf; CP_Radial_D5.0mm_P2.00mm
D1, D2, D3, D4: D; D_DO-41_SOD81_P10.16mm_Horizontal
D5: LED; LED_D5.0mm
J1, J2: Screw_Terminal_01x02; TerminalBlock_Phoenix_MKDS-1,5-2_1x02_P5.00mm_Horizontal
R1: 330ohm; R_Axial_DIN0207_L6.3mm_D2.5mm_P7.62mm_Horizontal
U1: L7805; TO-220-3_Vertical

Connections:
Earth: C1.2, C2.2, D3.1 (K), D4.2 (A), D5.1 (K), J1.2, J2.2, U1.2 (GND)
unnamed: D1.2 (A), D3.2 (A)
unnamed: D1.1 (K), D2.2 (A), J1.1
unnamed: C1.1, D2.1 (K), D4.1 (K), U1.1 (IN)
unnamed: D5.2 (A), R1.2
unnamed: C2.1, J2.1, R1.1, U1.3 (OUT)

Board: 2 copper layers, 11 parts (0 on the bottom side), 6 nets, no tracks yet.

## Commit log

2026-06-19 feat: Initial commit — 10 KiCad PCB design projects with comprehensive README
2026-06-19 docs: Update Voltage Regulator to flat single-sheet design, remove Copy variant
2026-06-19 style: Format markdown tables and fix clone URL

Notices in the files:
README.md:
MIT License
